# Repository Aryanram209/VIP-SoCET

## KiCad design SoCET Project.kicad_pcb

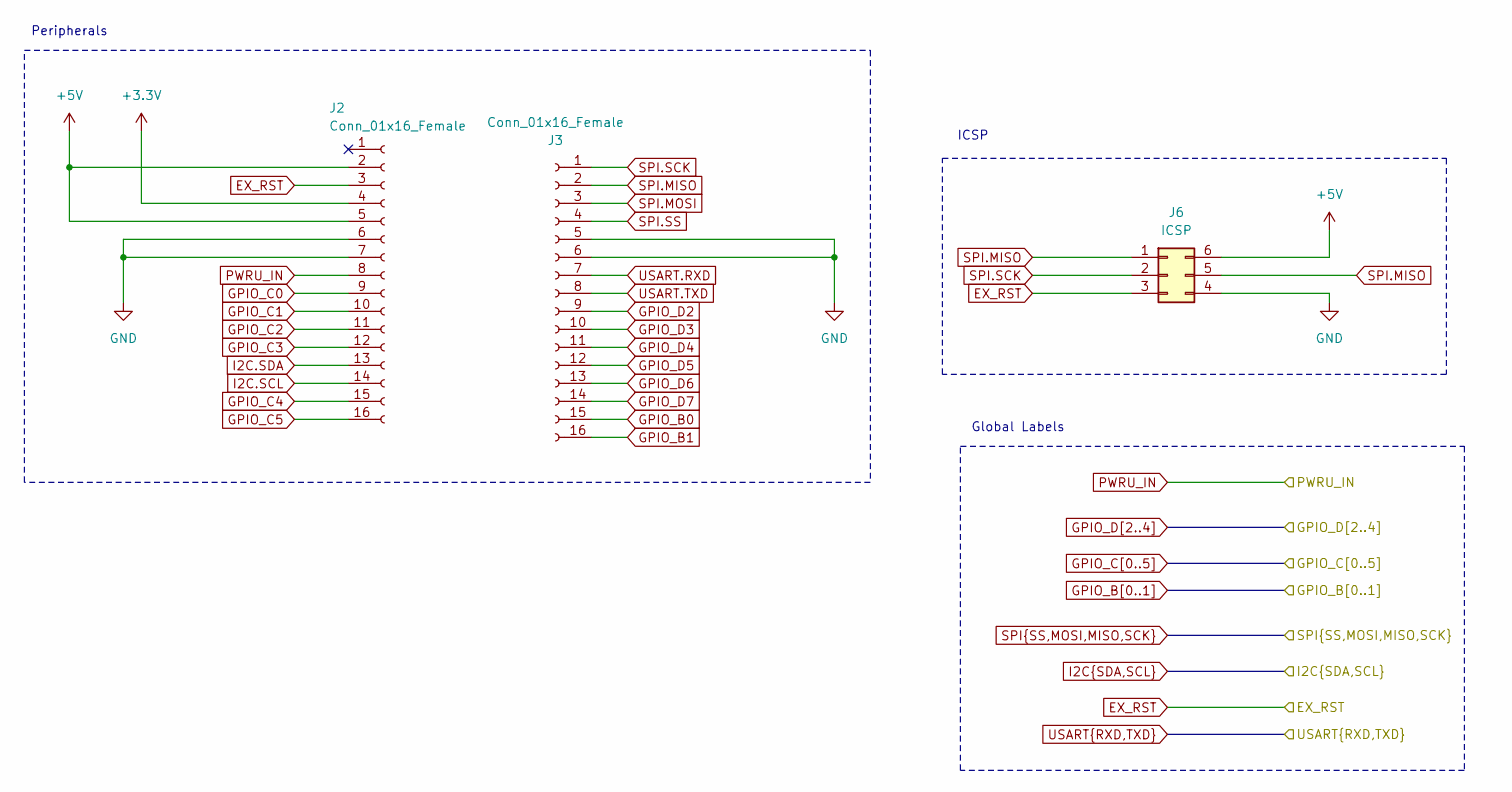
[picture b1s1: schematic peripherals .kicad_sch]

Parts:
J2, J3: Conn_01x16_Female; PinHeader_1x16_P2.54mm_Vertical
J6: ICSP; PinSocket_2x03_P2.54mm_Vertical

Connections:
+3.3V: J2.4; also elsewhere on the board
+5V: J2.2, J2.5, J6.6; also elsewhere on the board
EX_RST: J2.3, J6.3; also elsewhere on the board
GPIO_B0: J3.15; also elsewhere on the board
GPIO_B1: J3.16; also elsewhere on the board
GPIO_C0: J2.9; also elsewhere on the board
GPIO_C1: J2.10; also elsewhere on the board
GPIO_C2: J2.11; also elsewhere on the board
GPIO_C3: J2.12; also elsewhere on the board
GPIO_C4: J2.15; also elsewhere on the board
GPIO_C5: J2.16; also elsewhere on the board
GPIO_D2: J3.9; also elsewhere on the board
GPIO_D3: J3.10; also elsewhere on the board
GPIO_D4: J3.11; also elsewhere on the board
GPIO_D5: J3.12; also elsewhere on the board
GPIO_D6: J3.13; also elsewhere on the board
GPIO_D7: J3.14; also elsewhere on the board
I2C.SCL: J2.14
I2C.SDA: J2.13
PWRU_IN: J2.8; also elsewhere on the board
SPI.MISO: J3.2, J6.1, J6.5
SPI.MOSI: J3.3
SPI.SCK: J3.1, J6.2
SPI.SS: J3.4
USART.RXD: J3.7; also elsewhere on the board
USART.TXD: J3.8; also elsewhere on the board

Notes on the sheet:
Peripherals
Global Labels
ICSP

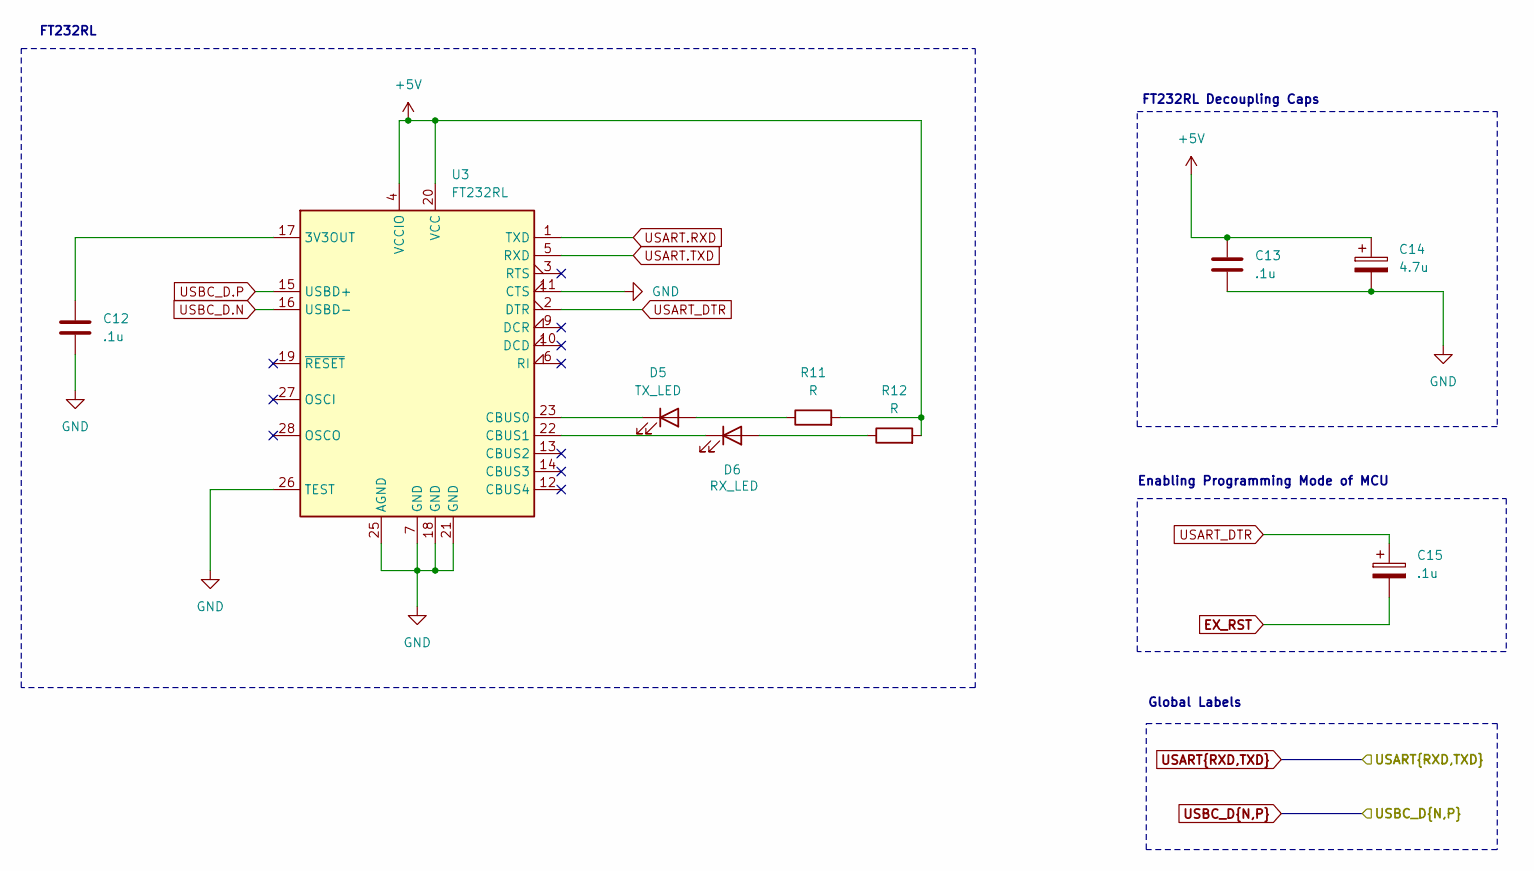
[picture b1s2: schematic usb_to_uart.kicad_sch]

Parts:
C12, C13: .1u; C_0402_1005Metric
C14: 4.7u; CP_Elec_6.3x7.7
C15: .1u; CP_Elec_6.3x7.7
D5: TX_LED; LED_0402_1005Metric
D6: RX_LED; LED_0402_1005Metric
R11, R12: R; R_0402_1005Metric
U3: FT232RL; SSOP-28_5.3x10.2mm_P0.65mm

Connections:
+5V: C13.1, C14.1, R11.2, R12.2, U3.4 (VCCIO), U3.20 (VCC); also elsewhere on the board
EX_RST: C15.2; also elsewhere on the board
unnamed: D5.2 (A), R11.1
unnamed: D5.1 (K), U3.23 (CBUS0)
unnamed: D6.2 (A), R12.1
unnamed: D6.1 (K), U3.22 (CBUS1)
unnamed: C12.1, U3.17 (3V3OUT)
USART.RXD: U3.1 (TXD); also elsewhere on the board
USART.TXD: U3.5 (RXD); also elsewhere on the board
USART_DTR: C15.1, U3.2 (DTR)

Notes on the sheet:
FT232RL Decoupling Caps
Enabling Programming Mode of MCU
Global Labels
FT232RL

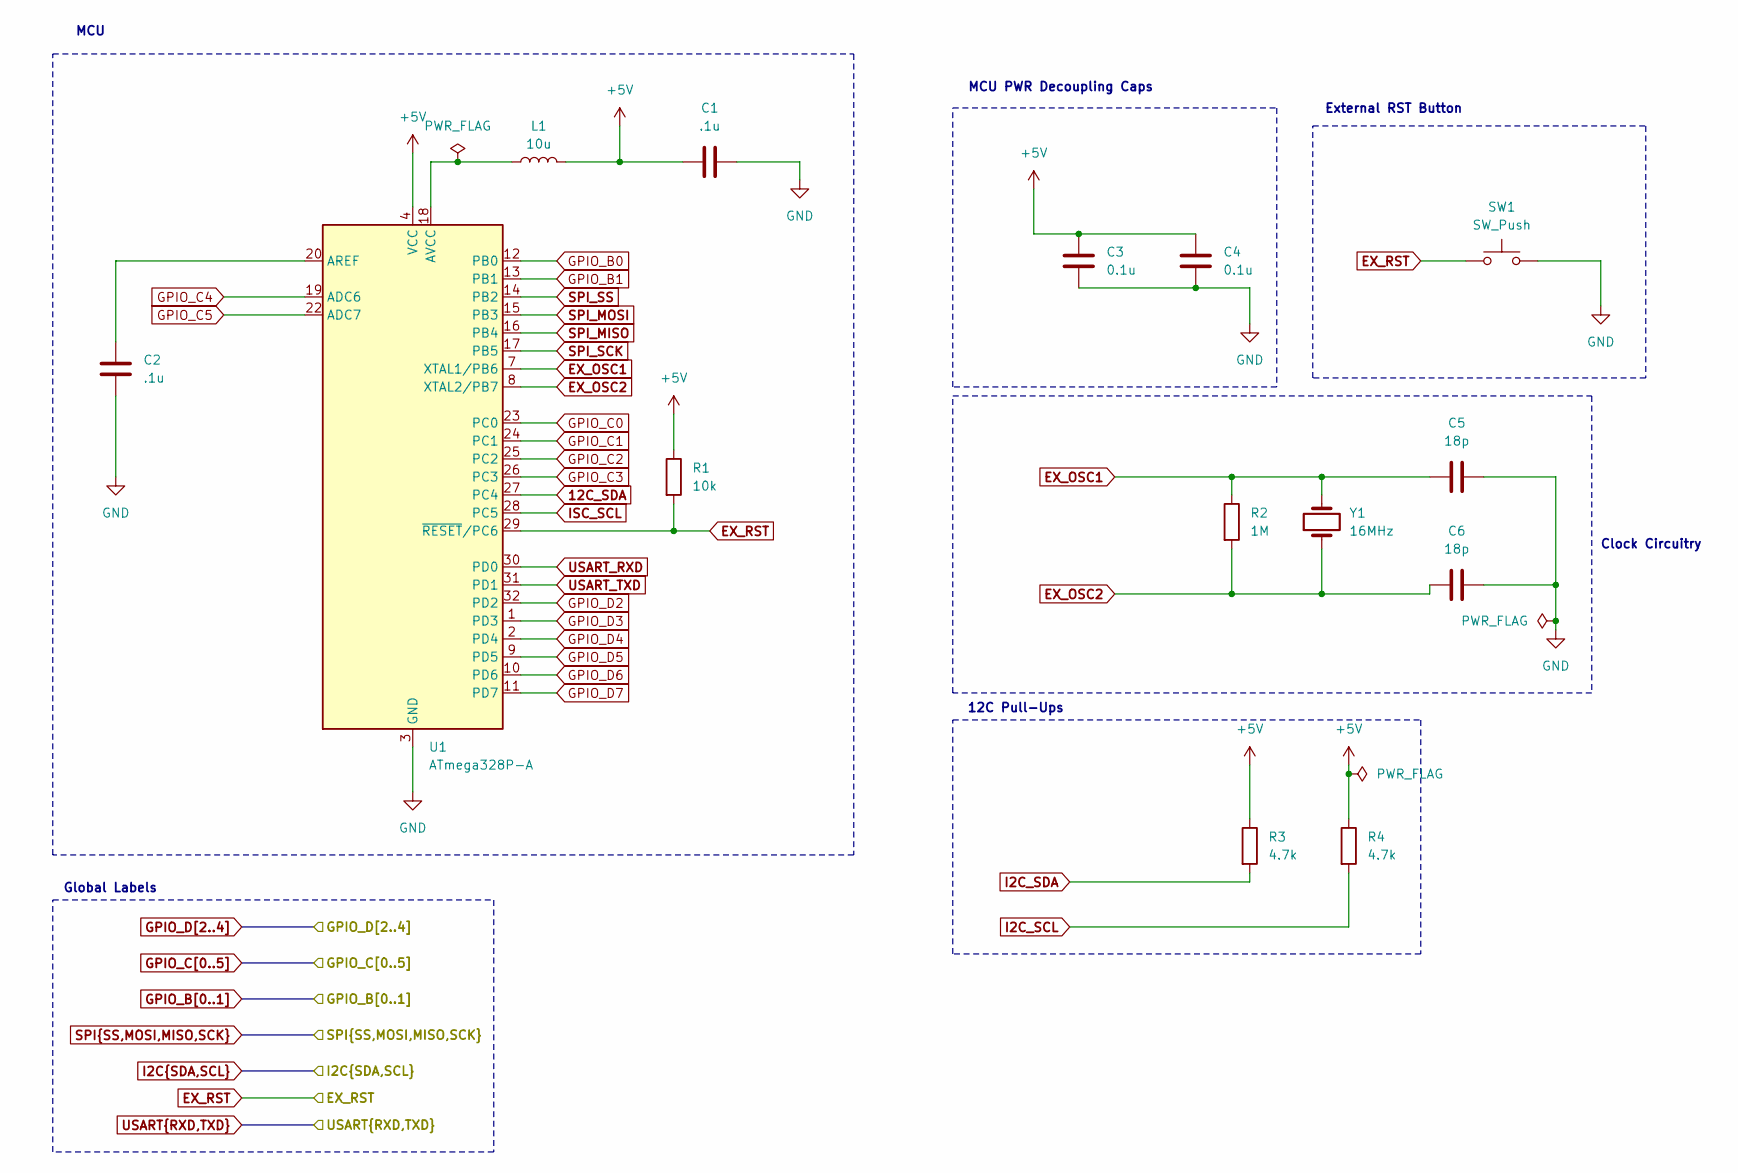
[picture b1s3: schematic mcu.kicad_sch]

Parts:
C1, C2: .1u; C_0402_1005Metric
C3, C4: 0.1u; C_0402_1005Metric
C5, C6: 18p; C_0402_1005Metric
L1: 10u; L_0603_1608Metric
R1: 10k; R_0402_1005Metric
R2: 1M; R_0402_1005Metric
R3, R4: 4.7k; R_0402_1005Metric
SW1: SW_Push; SW_Push_SPST_NO_Alps_SKRK
U1: ATmega328P-A; TQFP-32_7x7mm_P0.8mm
Y1: 16MHz; Crystal_SMD_2016-4Pin_2.0x1.6mm

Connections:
12C_SDA: U1.27 (PC4)
+5V: C1.1, C3.1, C4.1, L1.2, R1.1, R3.1, R4.1, U1.4 (VCC), U1.6 (VCC); also elsewhere on the board
EX_OSC1: C5.1, R2.1, U1.7 (XTAL1/PB6), Y1.2
EX_OSC2: C6.1, R2.2, U1.8 (XTAL2/PB7), Y1.1
EX_RST: R1.2, SW1.1, U1.29 (~RESET/PC6); also elsewhere on the board
GPIO_B0: U1.12 (PB0); also elsewhere on the board
GPIO_B1: U1.13 (PB1); also elsewhere on the board
GPIO_C0: U1.23 (PC0); also elsewhere on the board
GPIO_C1: U1.24 (PC1); also elsewhere on the board
GPIO_C2: U1.25 (PC2); also elsewhere on the board
GPIO_C3: U1.26 (PC3); also elsewhere on the board
GPIO_C4: U1.19 (ADC6); also elsewhere on the board
GPIO_C5: U1.22 (ADC7); also elsewhere on the board
GPIO_D2: U1.32 (PD2); also elsewhere on the board
GPIO_D3: U1.1 (PD3); also elsewhere on the board
GPIO_D4: U1.2 (PD4); also elsewhere on the board
GPIO_D5: U1.9 (PD5); also elsewhere on the board
GPIO_D6: U1.10 (PD6); also elsewhere on the board
GPIO_D7: U1.11 (PD7); also elsewhere on the board
I2C_SCL: R4.2
I2C_SDA: R3.2
ISC_SCL: U1.28 (PC5)
unnamed: C2.1, U1.20 (AREF)
unnamed: L1.1, U1.18 (AVCC)
SPI_MISO: U1.16 (PB4)
SPI_MOSI: U1.15 (PB3)
SPI_SCK: U1.17 (PB5)
SPI_SS: U1.14 (PB2)
USART_RXD: U1.30 (PD0)
USART_TXD: U1.31 (PD1)

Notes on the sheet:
External RST Button
MCU
Global Labels
12C Pull-Ups
MCU PWR Decoupling Caps
Clock Circuitry

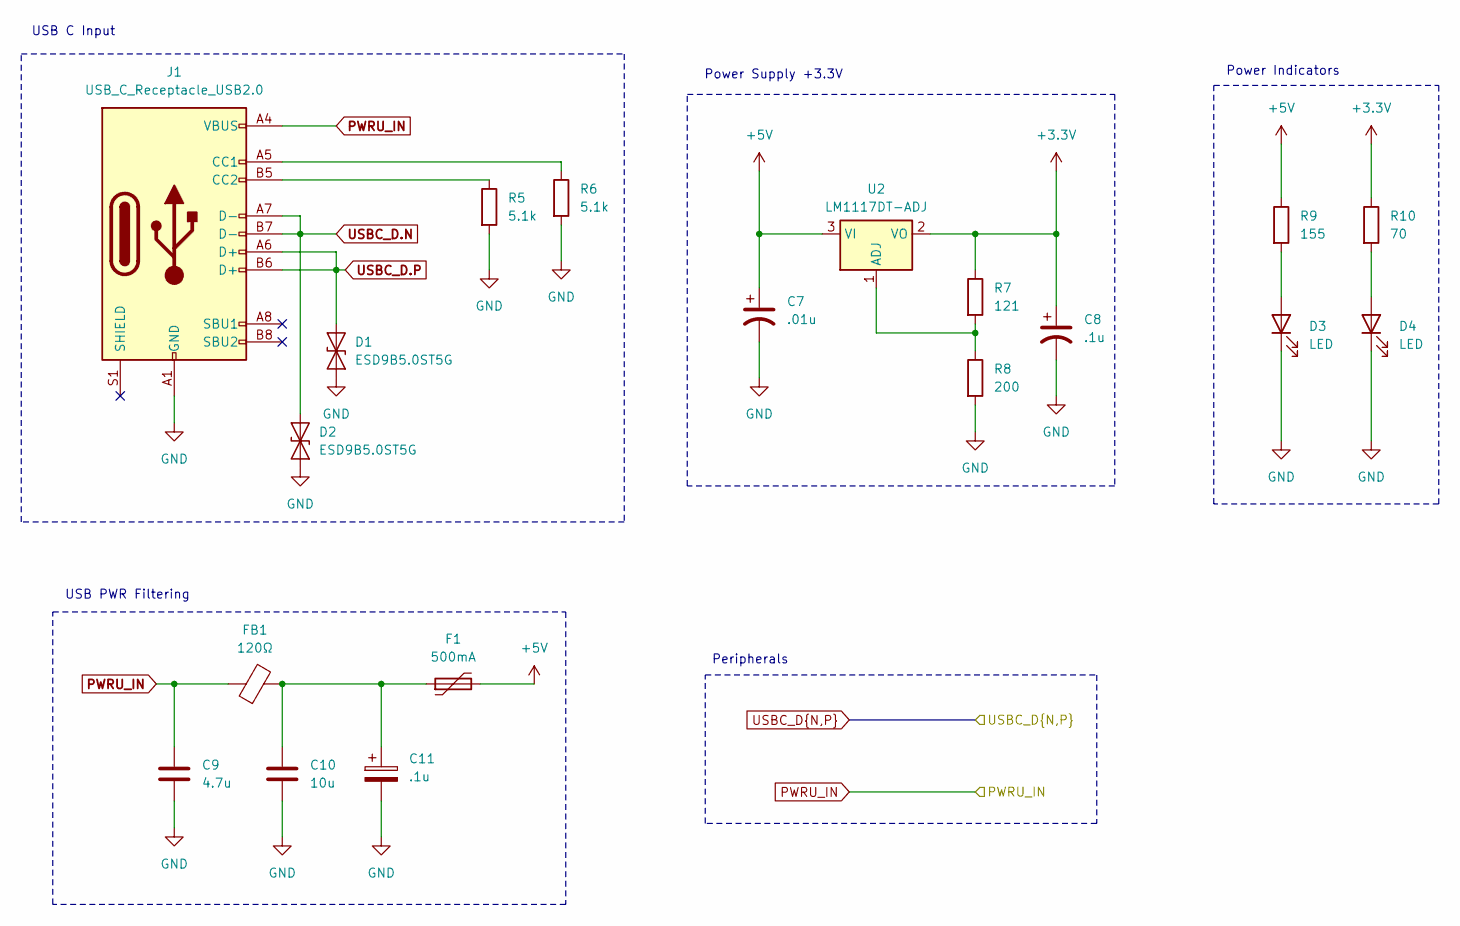
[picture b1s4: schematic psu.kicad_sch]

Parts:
C7: .01u; C_0603_1608Metric
C8: .1u; C_0402_1005Metric
C9: 4.7u; CP_Elec_6.3x7.7
C10: 10u; CP_Elec_6.3x7.7
C11: .1u; CP_Elec_6.3x7.7
D1, D2: ESD9B5.0ST5G; D_SOD-923
D3, D4: LED; LED_0402_1005Metric
F1: 500mA; Fuse_1812_4532Metric
FB1: 120Ω; L_0603_1608Metric
J1: USB_C_Receptacle_USB2.0; USB_C_Receptacle_Palconn_UTC16-G
R5, R6: 5.1k; R_0402_1005Metric
R7: 121; R_0402_1005Metric
R8: 200; R_0402_1005Metric
R9: 155; R_0402_1005Metric
R10: 70; R_0402_1005Metric
U2: LM1117DT-ADJ; SOT-223

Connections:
+3.3V: C8.1, R7.1, R10.1, U2.2 (VO); also elsewhere on the board
+5V: C7.1, F1.2, R9.1, U2.3 (VI); also elsewhere on the board
unnamed: C10.1, C11.1, F1.1, FB1.2
unnamed: D3.2 (A), R9.2
unnamed: D4.2 (A), R10.2
unnamed: J1.A5 (CC1), R6.1
unnamed: J1.B5 (CC2), R5.1
unnamed: R7.2, R8.1, U2.1 (ADJ)
PWRU_IN: C9.1, FB1.1, J1.A4 (VBUS), J1.A9 (VBUS), J1.B4 (VBUS), J1.B9 (VBUS); also elsewhere on the board

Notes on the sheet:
Power Supply +3.3V
Power Indicators
USB C Input
Peripherals
USB PWR Filtering

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
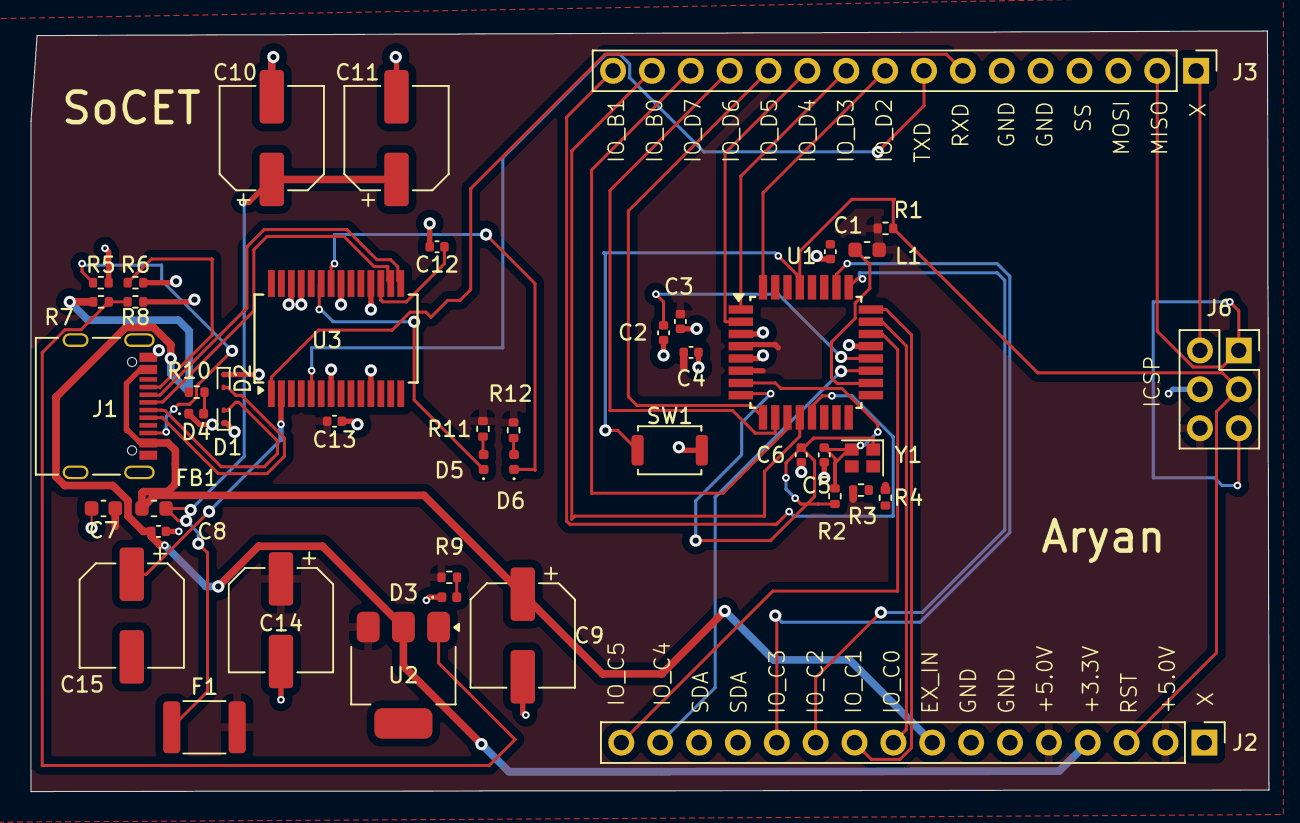
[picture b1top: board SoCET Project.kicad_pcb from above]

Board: 2 copper layers, 80.9 x 49.7 mm, 45 parts (0 on the bottom side), 41 nets.

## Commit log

2025-02-24 Add files via upload
    Completed SCH and DSG
